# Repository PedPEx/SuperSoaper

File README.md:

# SuperSoaper
An open source automatic soap dispenser

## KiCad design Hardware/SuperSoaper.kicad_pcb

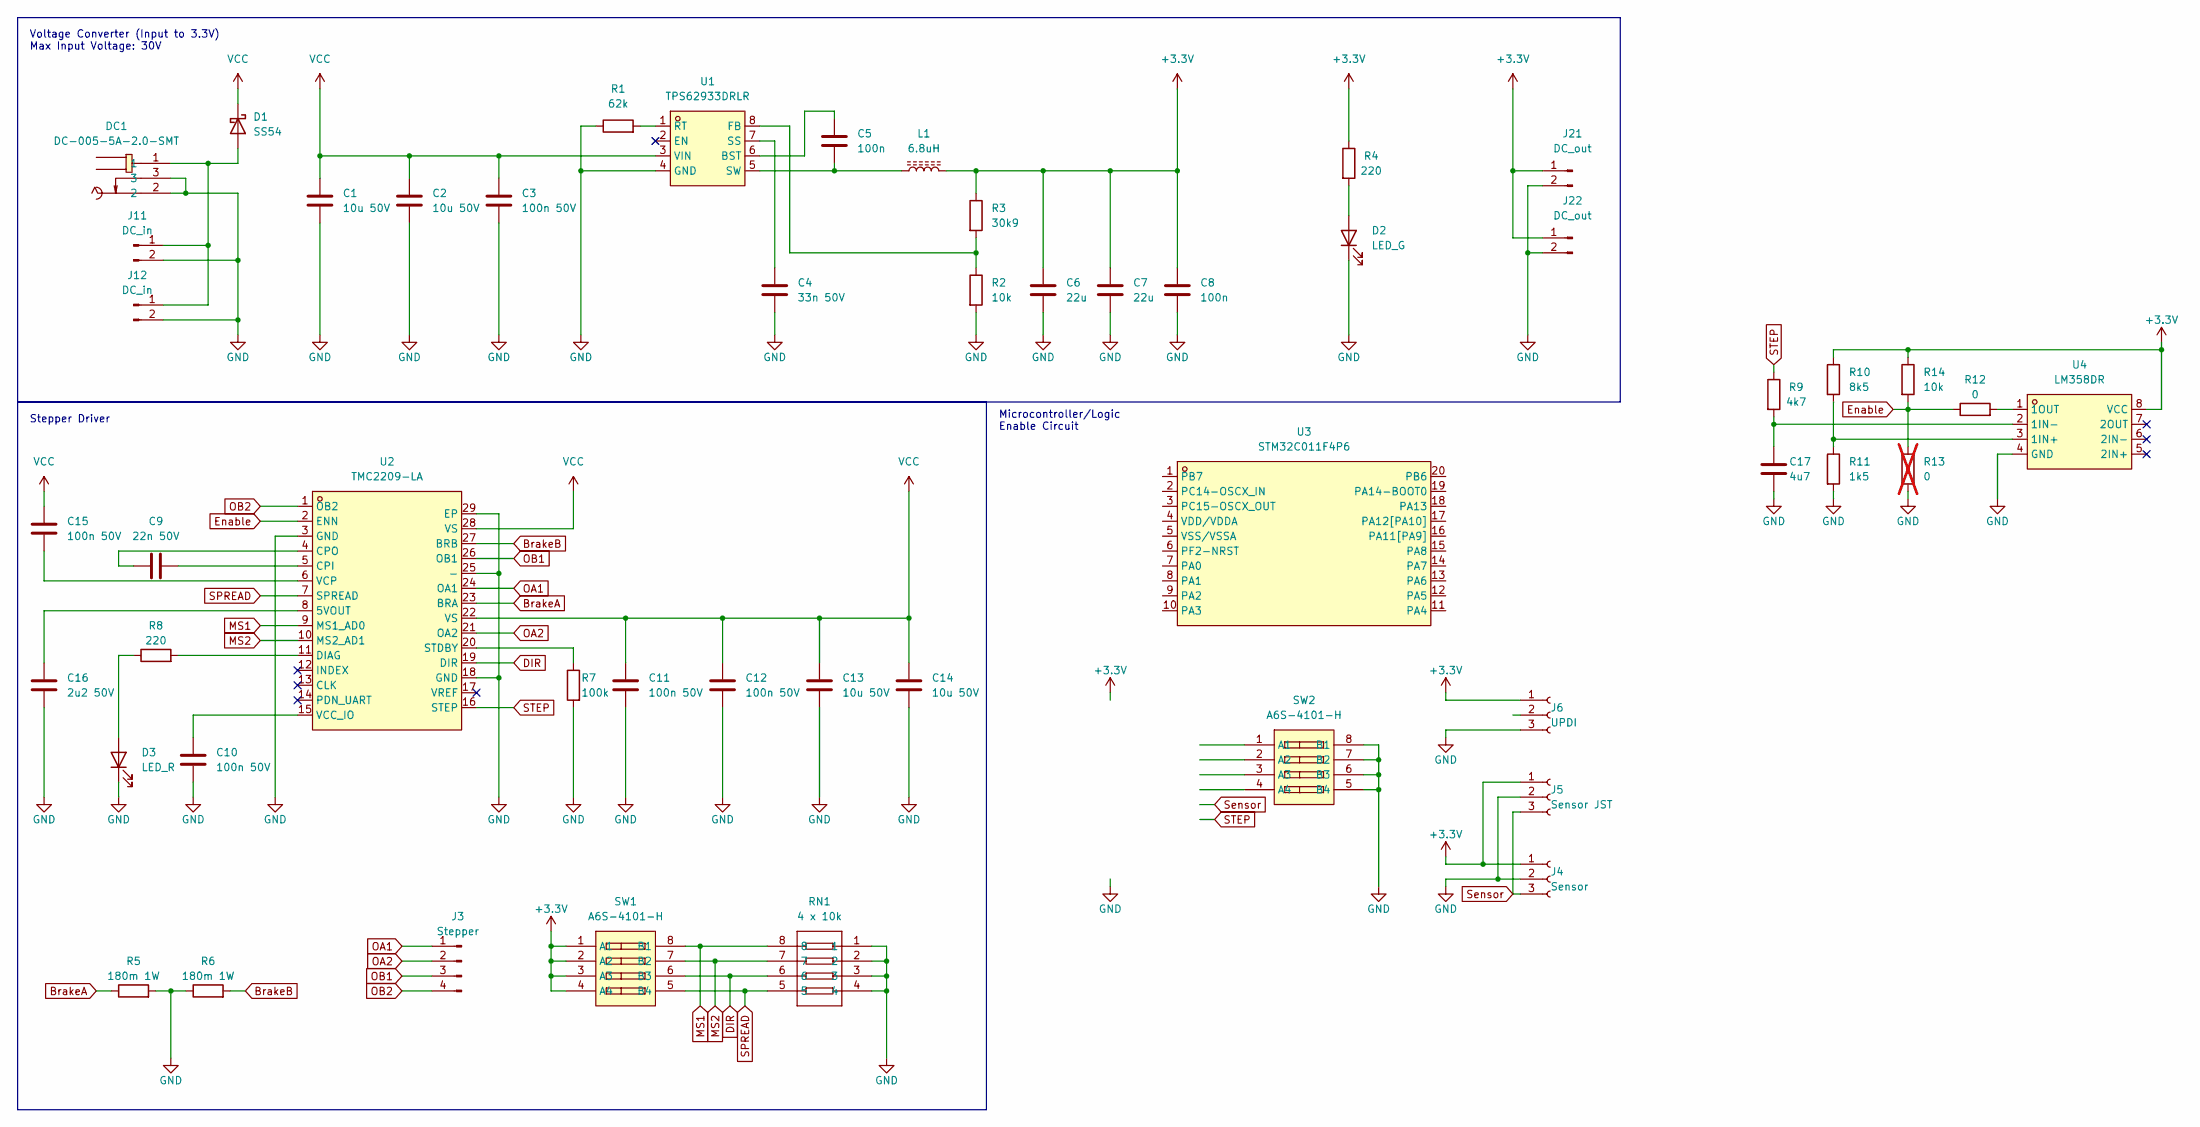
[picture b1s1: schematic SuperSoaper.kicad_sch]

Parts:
C1, C2: 10u 50V; C_0603_1608Metric
C3, C10, C11, C12, C15: 100n 50V; C_0603_1608Metric
C4: 33n 50V; C_0603_1608Metric
C5, C8: 100n; C_0603_1608Metric
C6, C7: 22u; C_0603_1608Metric
C9: 22n 50V; C_0603_1608Metric
C13, C14: 10u 50V; C_1210_3225Metric
C16: 2u2 50V; C_0603_1608Metric
C17: 4u7; C_0603_1608Metric
D1: SS54; SMA_L4.4-W2.8-LS5.4-R-RD
D2: LED_G; LED_0603_1608Metric
D3: LED_R; LED_0603_1608Metric
DC1: DC-005-5A-2.0-SMT; DC-IN-TH_DC-005-5A-2.0-SMT; LCSC Part C319134
J3: Stepper; CONN-TH_B4B-XH-A-LF-SN
J4: Sensor; HDR-TH_3P-P2.54-H-F-W10.0-N
J5: Sensor JST; CONN-TH_S3B-XH-A-1-LF-SN
J6: UPDI; HDR-TH_3P-P2.54-V-F
J11, J12: DC_in; CONN-TH_B2B-XH-A-LF-SN
J21, J22: DC_out; CONN-TH_B2B-XH-A-LF-SN
L1: 6.8uH; IND-SMD_L7.4-W7.0
R1: 62k; R_0603_1608Metric
R2, R14: 10k; R_0603_1608Metric
R3: 30k9; R_0603_1608Metric
R4, R8: 220; R_0603_1608Metric
R5, R6: 180m 1W; R_1206_3216Metric
R7: 100k; R_0603_1608Metric
R9: 4k7; R_0603_1608Metric
R10: 8k5; R_0603_1608Metric
R11: 1k5; R_0603_1608Metric
R12: 0; R_0603_1608Metric
R13: 0; R_0603_1608Metric; not fitted
RN1: 4 x 10k; RES-ARRAY-SMD_0603-8P-L3.2-W1.6-BL; LCSC Part C69593
SW1, SW2: A6S-4101-H; SW-SMD_8P-L11.1-W6.2-P2.54-LS9.8; LCSC Part C306873
U1: TPS62933DRLR; SOT-583-8_L2.1-W1.2-P0.50-LS1.6-BR; LCSC Part C3200405
U2: TMC2209-LA; QFN-28_L5.0-W5.0-P0.50-BL-EP; LCSC Part C465949
U3: STM32C011F4P6; TSSOP-20_L6.5-W4.4-P0.65-LS6.4-BL; LCSC Part C5452432
U4: LM358DR; SOIC-8_3.9x4.9mm_P1.27mm; LCSC Part C5423

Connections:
+3.3V: C6.2, C7.2, C8.1, J4.1, J5.1, J6.1, J21.1, J22.1, L1.2, R3.1, R4.1, R10.1, R14.1, SW1.1 (A1), SW1.2 (A2), SW1.3 (A3), SW1.4 (A4), U4.8 (VCC)
BrakeA: R5.1, U2.23 (BRA)
BrakeB: R6.2, U2.27 (BRB)
DIR: RN1.6, SW1.6 (B3), U2.19 (DIR)
Enable: R12.1, R13.1, R14.2, U2.2 (ENN)
GND: C1.2, C2.2, C3.2, C4.1, C6.1, C7.1, C8.2, C10.2, C11.2, C12.2, C13.2, C14.2, C16.2, C17.2, D2.1 (K), D3.1 (K), DC1.2, DC1.3, J4.2, J5.2, J6.3, J11.2, J12.2, J21.2, J22.2, R1.1, R2.2, R5.2, R6.1, R7.2, R11.2, R13.2, RN1.1, RN1.2, RN1.3, RN1.4, SW2.5 (B4), SW2.6 (B3), SW2.7 (B2), SW2.8 (B1), U1.4 (GND), U2.3 (GND), U2.18 (GND), U2.25 (-), U2.29 (EP), U4.4 (GND)
MS1: RN1.8, SW1.8 (B1), U2.9 (MS1_AD0)
MS2: RN1.7, SW1.7 (B2), U2.10 (MS2_AD1)
unnamed: D1.2 (A), DC1.1, J11.1, J12.1
unnamed: D2.2 (A), R4.2
unnamed: D3.2 (A), R8.1
unnamed: C5.1, U1.6 (BST)
unnamed: R2.1, R3.2, U1.8 (FB)
unnamed: R1.2, U1.1 (RT)
unnamed: C4.2, U1.7 (SS)
unnamed: C5.2, L1.1, U1.5 (SW)
unnamed: C16.1, U2.8 (5VOUT)
unnamed: C9.1, U2.5 (CPI)
unnamed: C9.2, U2.4 (CPO)
unnamed: R8.2, U2.11 (DIAG)
unnamed: R7.1, U2.20 (STDBY)
unnamed: C10.1, U2.15 (VCC_IO)
unnamed: C15.2, U2.6 (VCP)
unnamed: R10.2, R11.1, U4.3 (1IN+)
unnamed: C17.1, R9.2, U4.2 (1IN-)
unnamed: R12.2, U4.1 (1OUT)
OA1: J3.1, U2.24 (OA1)
OA2: J3.2, U2.21 (OA2)
OB1: J3.3, U2.26 (OB1)
OB2: J3.4, U2.1 (OB2)
SPREAD: RN1.5, SW1.5 (B4), U2.7 (SPREAD)
STEP: R9.1, U2.16 (STEP)
Sensor: J4.3, J5.3
VCC: C1.1, C2.1, C3.1, C11.1, C12.1, C13.1, C14.1, C15.1, D1.1 (K), U1.3 (VIN), U2.22 (VS), U2.28 (VS)

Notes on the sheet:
Stepper Driver
Voltage Converter (Input to 3.3V) Max Input Voltage: 30V
Microcontroller/Logic Enable Circuit

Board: 2 copper layers, 51 parts (0 on the bottom side), 34 nets, no tracks yet.

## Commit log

2023-12-21 Initial test commit
2023-12-21 Added initial software projects
2023-12-24 First basic Schematic finished
2023-12-25 minor details changed
2024-02-08 CHanged from ATtiny 2X2 to STM32C011F4P6
2024-02-10 init for STM32C011F4Px corrected fault in gitignore
